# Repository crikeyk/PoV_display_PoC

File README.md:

# PoV display

A hand-waved persistence-of-vision wand. A strip of 16 LEDs and an accelerometer draw a word or a picture in the air.

## What goes on the wand

`Firmware/device/` is the CircuitPython image for the RP2350 (Pico 2) wand. Copy the files inside that folder onto the `CIRCUITPY` drive. `code.py` there is version 7.

A Pico that has never been used needs CircuitPython first. Hold BOOTSEL while plugging it in so a drive named `RP2350` appears, copy `Firmware/circuitpython-pico2-10.3.1.uf2` onto it, then copy `Firmware/device/`.

`README.txt` inside that folder is the note for whoever changes the words.

## What does not go on the wand

`Firmware/debug/` records a swing and draws it in a browser. `Firmware/tests/` are early hardware checks. `Firmware/ch572/` is a different board.

## Older firmware

Version 6 was the last stable program before version 7 froze the pace for each pass. It is the git tag `v6`. In that tag the program is `Firmware/device_pull_v1/code.py`.

`AGENTS.md` is the longer note for a person or a coding agent picking this up.

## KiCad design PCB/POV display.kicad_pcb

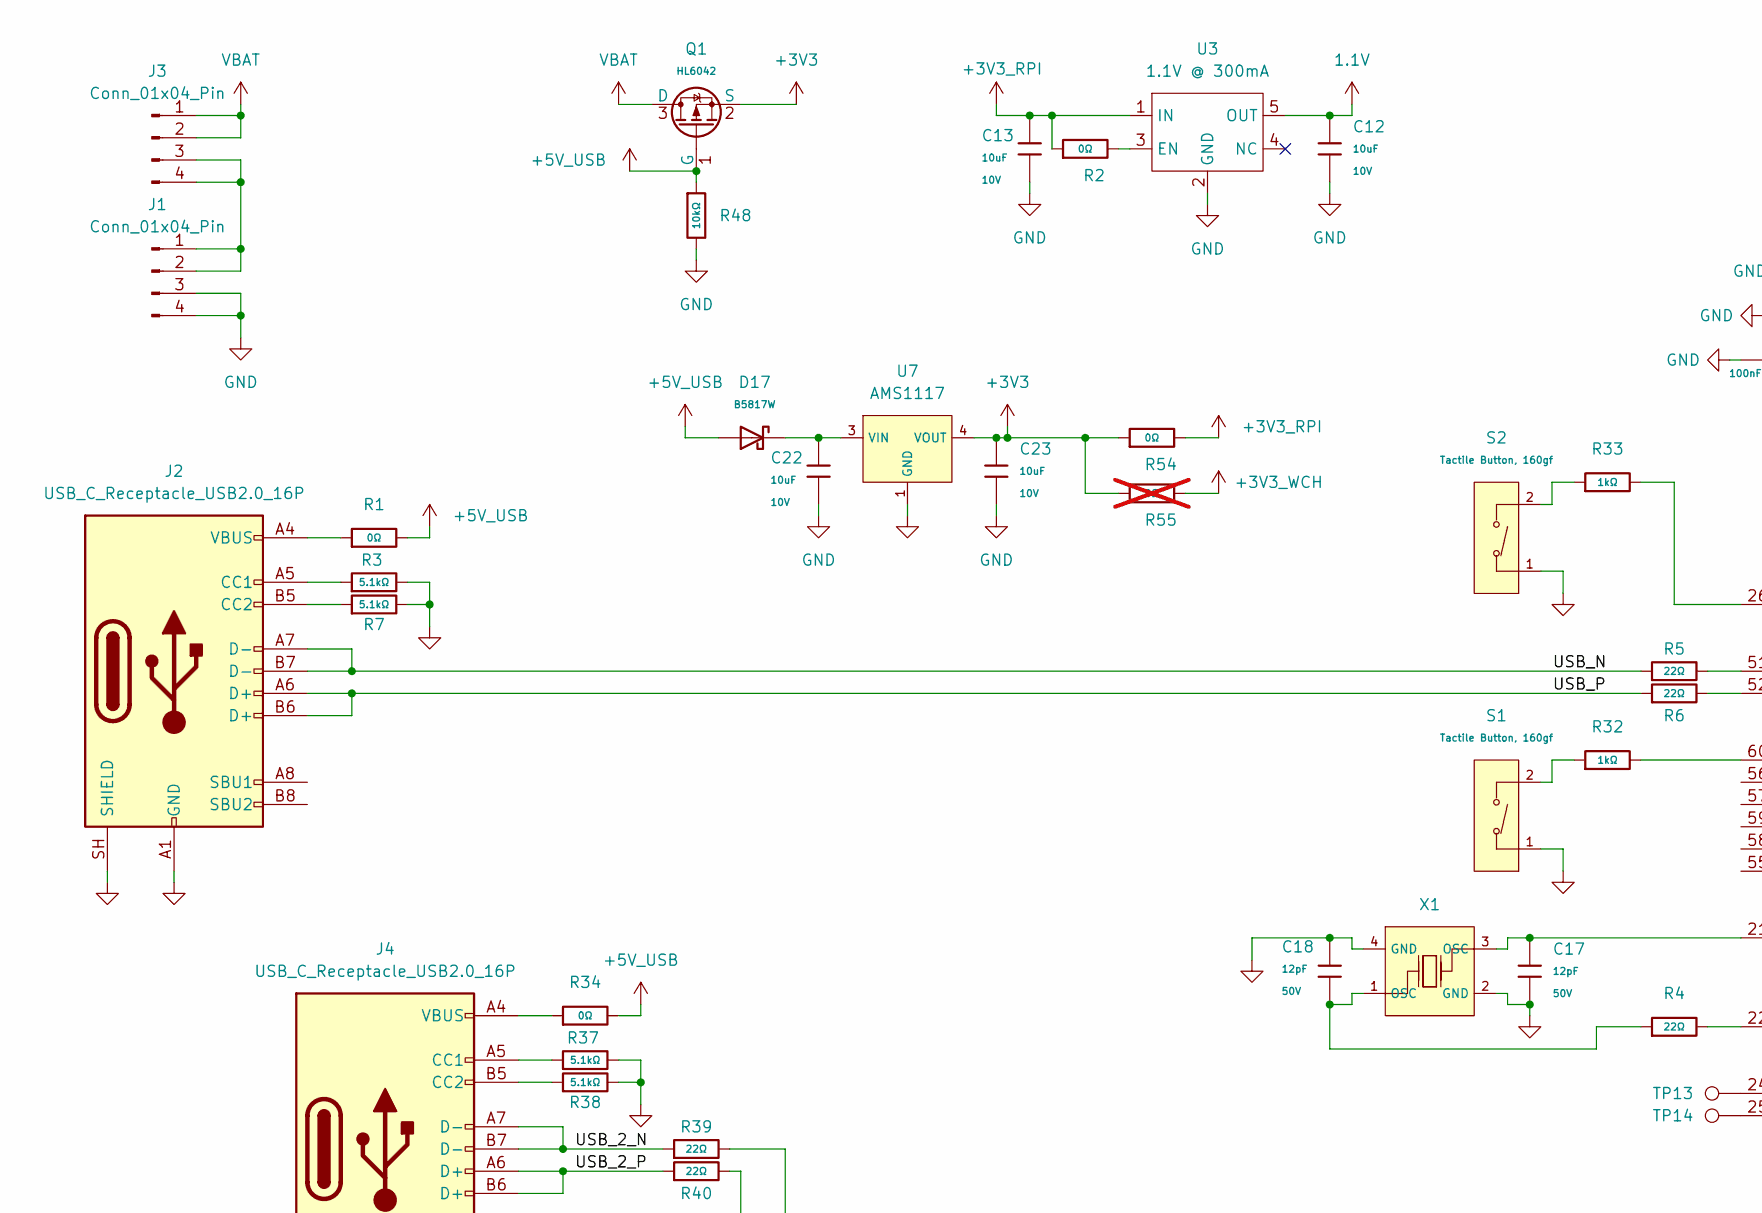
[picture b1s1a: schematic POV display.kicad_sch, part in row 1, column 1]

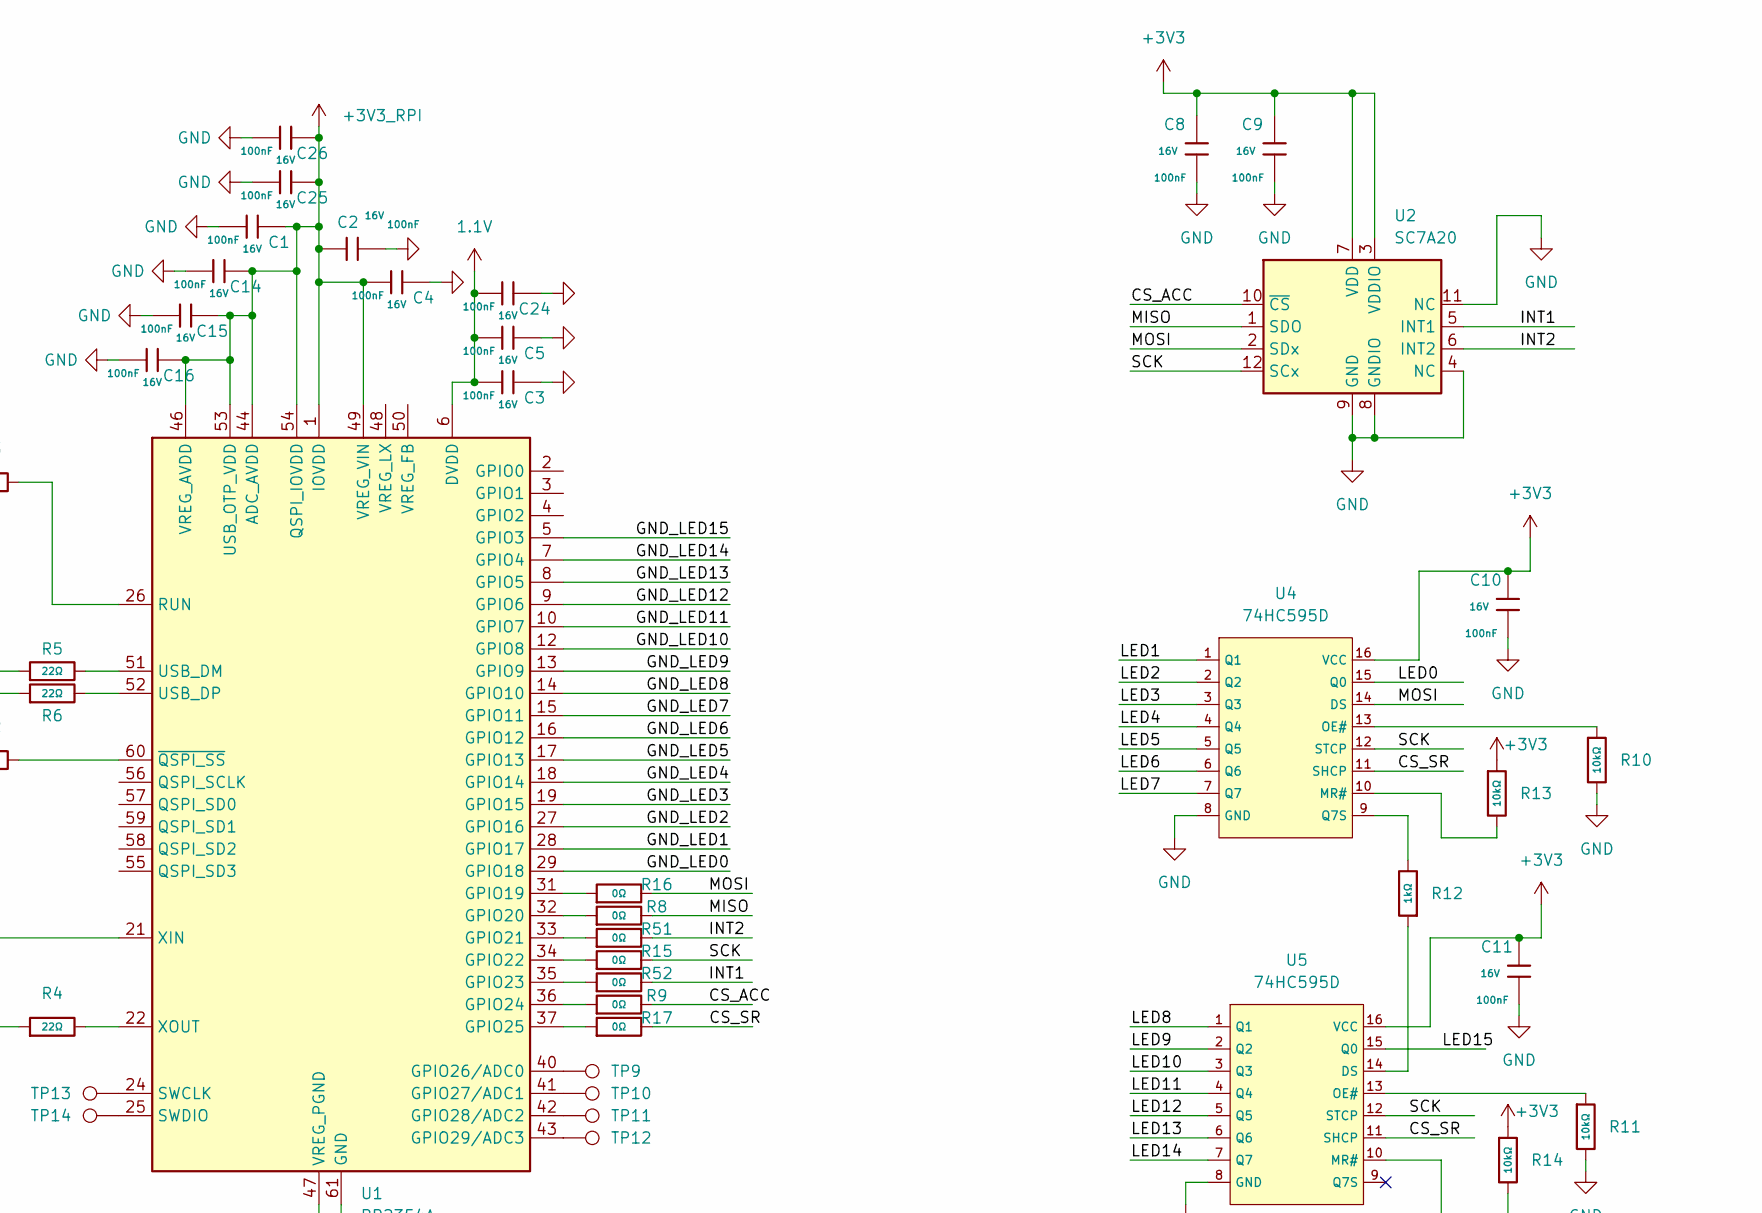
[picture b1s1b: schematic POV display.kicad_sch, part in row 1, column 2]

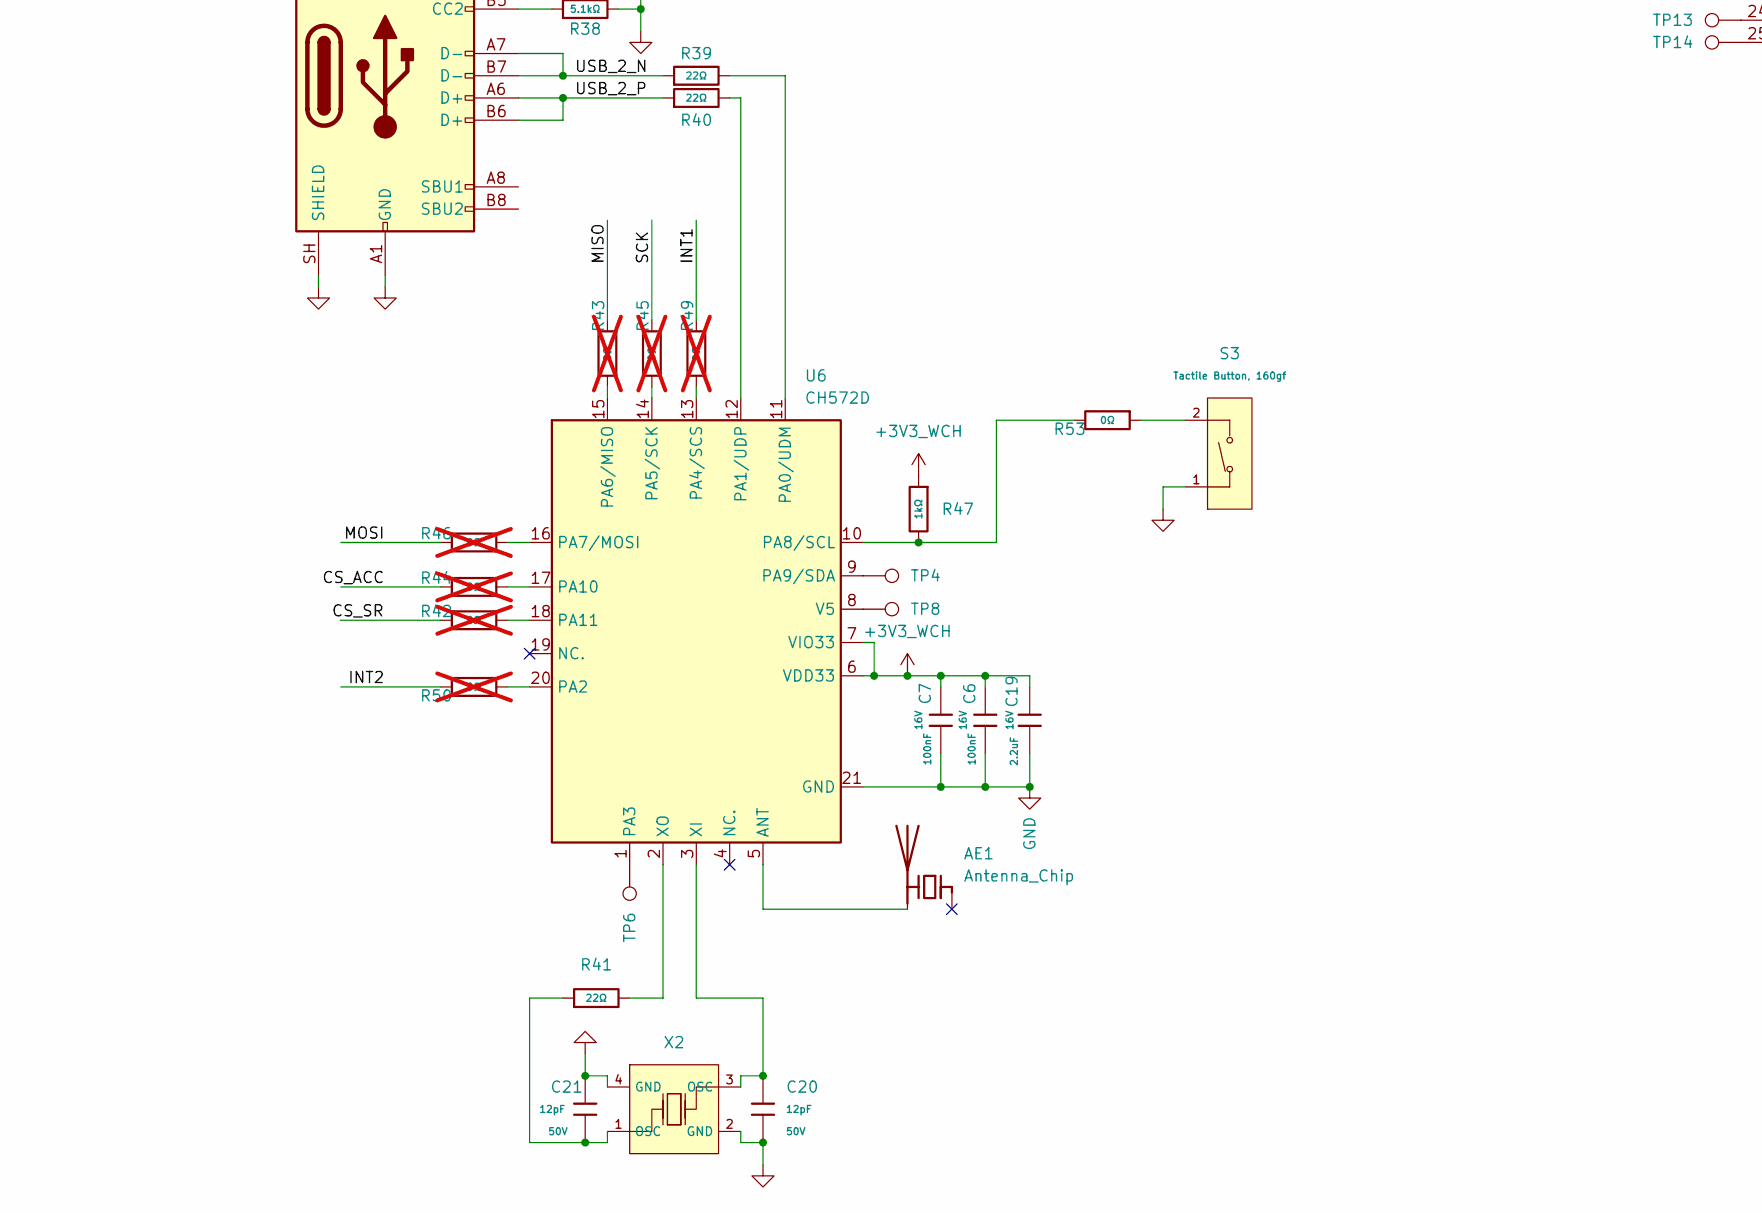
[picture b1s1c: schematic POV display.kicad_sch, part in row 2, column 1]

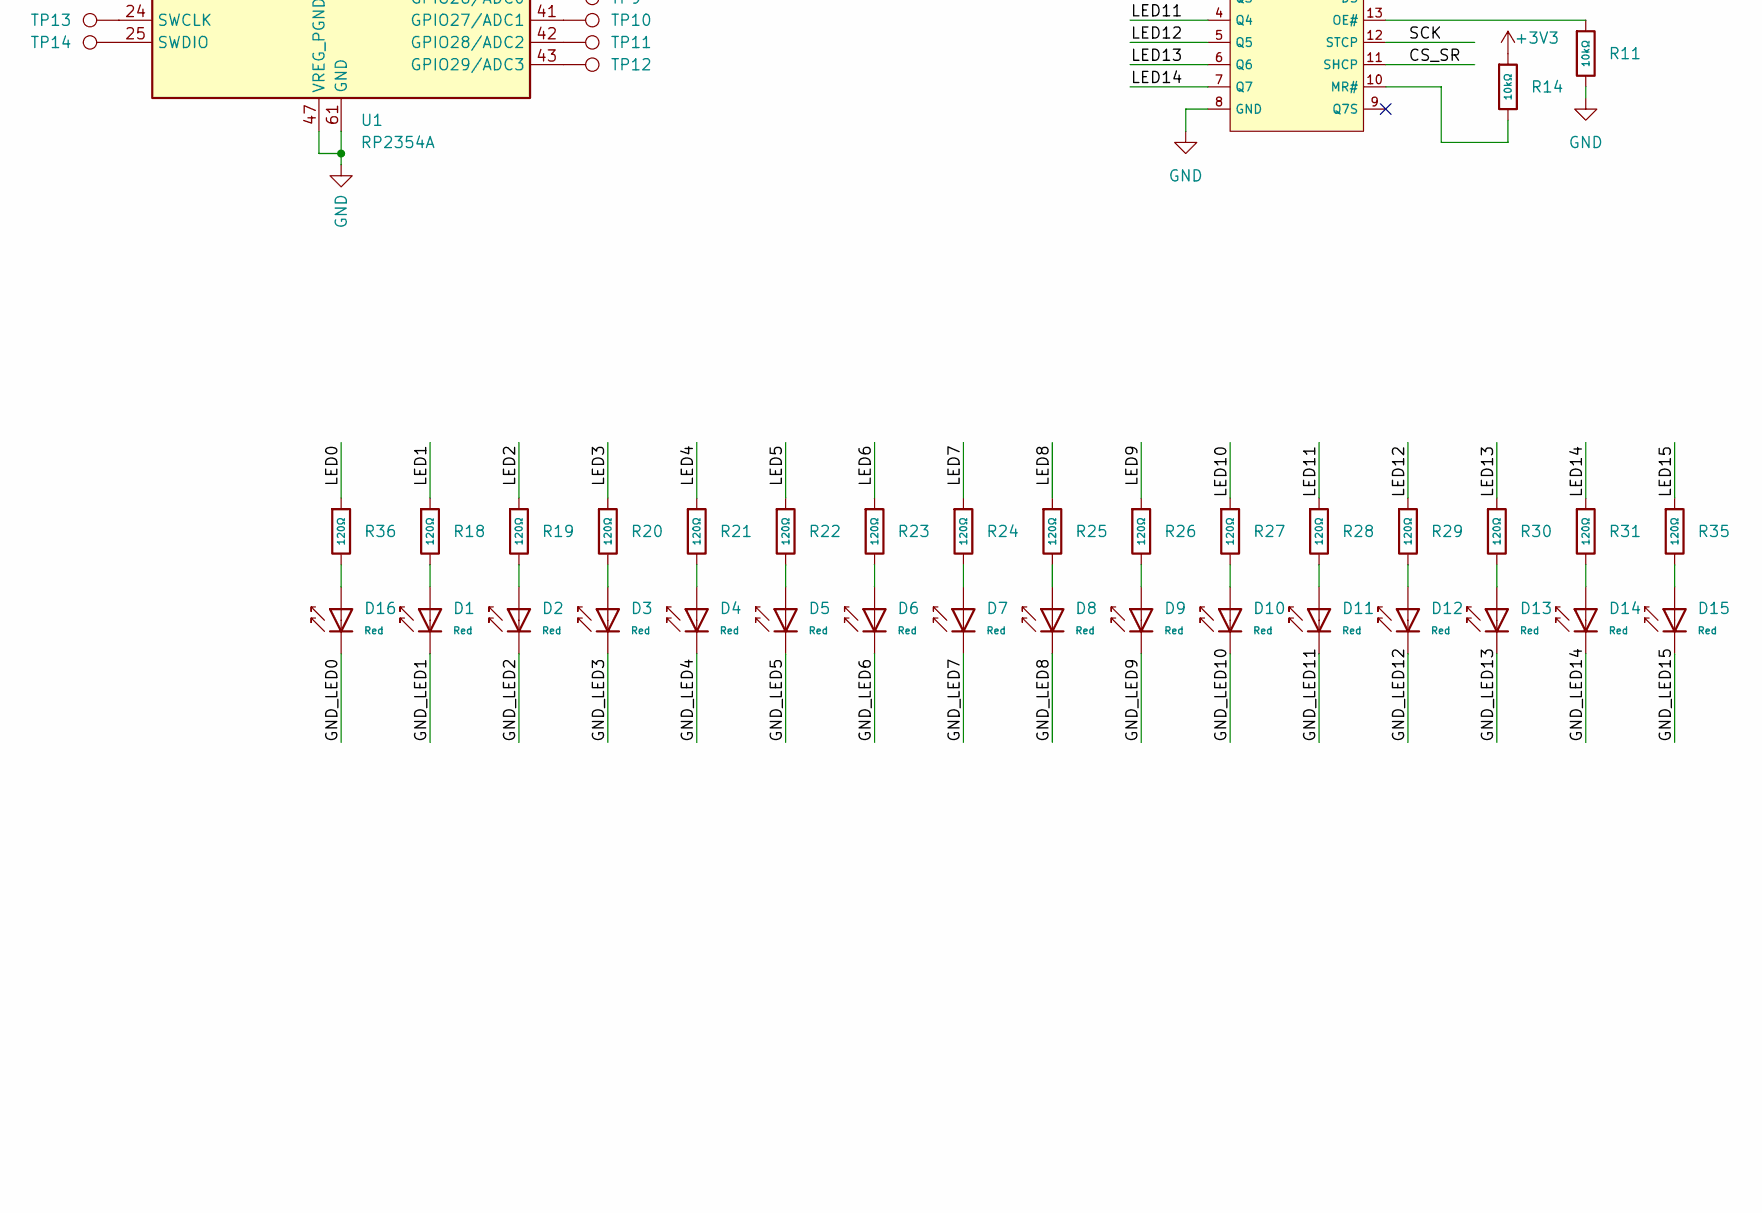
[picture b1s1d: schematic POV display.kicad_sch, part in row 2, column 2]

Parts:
AE1: Antenna_Chip; C_1206_3216Metric; LCSC C127629
C1, C2, C3, C4, C5, C6, C7, C8, C9, C10, C11, C14, C15, C16, C24, C25, C26: 100nF; C_0402; Voltage Rated 16V; Tolerance ±10%; Part CL05B104KO5NNNC; LCSC C1525
C12, C13, C22, C23: 10uF; C_0603; Voltage Rated 10V; Tolerance ±10%; Part CL10A106KP8NNNC; LCSC C19702
C17, C18, C20, C21: 12pF; C_0402; Voltage Rated 50V; Tolerance ±5%; Part 0402CG120J500NT; LCSC C1547
C19: 2.2uF; C_0603; Voltage Rated 16V; Tolerance ±10%; Part CL10A225KO8NNNC; LCSC C23630
D1, D2, D3, D4, D5, D6, D7, D8, D9, D10, D11, D12, D13, D14, D15, D16: Red; D_0603; Part KT-0603R; LCSC C2286
D17: B5817W; D_SOD-123; Forward Voltage (Vf@If) 0.45V@1.0A; Reverse Voltage (Vr) 20V; Part B5817W; LCSC C7420328
J1, J3: Conn_01x04_Pin; BC-8200 AAA Battery clip
J2, J4: USB_C_Receptacle_USB2.0_16P; USB_C_Receptacle_HRO_TYPE-C-31-M-12; LCSC C165948
Q1: HL6042; Q_SOT-23; Part HL6042; LCSC C28646264
R1, R2, R8, R9, R15, R16, R17, R34, R51, R52, R53, R54: 0Ω; R_0402; Overload Voltage (Max) 50V; Tolerance ±1%; Part 0402WGF0000TCE; LCSC C17168
R3, R7, R37, R38: 5.1kΩ; R_0402; Overload Voltage (Max) 50V; Tolerance ±1%; Part 0402WGF5101TCE; LCSC C25905
R4, R5, R6, R39, R40, R41: 22Ω; R_0402; Overload Voltage (Max) 50V; Tolerance ±1%; Part 0402WGF220JTCE; LCSC C25092
R10, R11, R13, R14: 10kΩ; R_0603; Overload Voltage (Max) 75V; Tolerance ±1%; Part 0603WAF1002T5E; LCSC C25804
R12: 1kΩ; R_0603; Overload Voltage (Max) 75V; Tolerance ±1%; Part 0603WAF1001T5E; LCSC C21190
R18, R19, R20, R21, R22, R23, R24, R25, R26, R27, R28, R29, R30, R31, R35, R36: 120Ω; R_0603; Overload Voltage (Max) 75V; Tolerance ±1%; Part 0603WAF1200T5E; LCSC C22787
R32, R33, R47: 1kΩ; R_0402; Overload Voltage (Max) 50V; Tolerance ±1%; Part 0402WGF1001TCE; LCSC C11702
R42, R43, R44, R45, R46, R49, R50, R55: 0Ω; R_0402; Overload Voltage (Max) 50V; Tolerance ±1%; Part 0402WGF0000TCE; LCSC C17168; not fitted
R48: 10kΩ; R_0402; Overload Voltage (Max) 50V; Tolerance ±1%; Part 0402WGF1002TCE; LCSC C25744
S1, S2, S3: Tactile Button, 160gf; SW_TS-1088-AR02016; Voltage Rating (Dc) 12V; Part TS-1088-AR02016; LCSC C720477
TP4, TP6, TP8, TP9, TP10, TP11, TP12, TP13, TP14: TestPoint; TestPoint_Pad_D1.0mm
U1: RP2354A; QFN-60-1EP_7x7mm_P0.4mm_EP3.4x3.4mm; LCSC C41378174
U2: SC7A20; LGA-12_2x2mm_P0.5mm; LCSC C19274408
U3: 1.1V @ 300mA; SOT-23-5; LCSC C485147
U4, U5: 74HC595D; SOIC-16_L9.9-W3.9-P1.27-LS6.0-BL; Supply Voltage 2V~6V; Part 74HC595D,118; LCSC C5947
U6: CH572D; QFN-20-1EP_3x3mm_P0.4mm_EP1.65x1.65mm
U7: AMS1117; SOT-223-3_L6.5-W3.4-P2.30-LS7.0-BR; Output Voltage 3.3V; Dropout Voltage 1.3V@(800mA); Part AMS1117-3.3; LCSC C6186
X1: X322512MSB4SI; CRYSTAL-SMD_4P-L3.2-W2.5-BL; Frequency Tolerance ±10ppm; Part X322512MSB4SI; LCSC C9002
X2: Y201632MFBCX; Crystal_SMD_2016-4Pin_2.0x1.6mm; Frequency Tolerance ±10ppm; Part Y201632MFBCX; LCSC C49158176

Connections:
1.1V: C3.2, C5.2, C12.1, C24.2, U1.6 (DVDD), U1.23 (DVDD), U1.39 (DVDD), U3.5 (OUT)
+3V3: C8.1, C9.1, C10.1, C11.1, C23.1, Q1.2 (S), R13.1, R14.1, R54.1, R55.1, U2.3 (VDDIO), U2.7 (VDD), U4.16 (VCC), U5.16 (VCC), U7.2 (VOUT), U7.4 (VOUT)
+3V3_RPI: C1.1, C2.1, C4.2, C13.1, C14.1, C15.1, C16.1, C25.1, C26.1, R2.1, R54.2, U1.1 (IOVDD), U1.11 (IOVDD), U1.20 (IOVDD), U1.30 (IOVDD), U1.38 (IOVDD), U1.44 (ADC_AVDD), U1.45 (IOVDD), U1.46 (VREG_AVDD), U1.49 (VREG_VIN), U1.53 (USB_OTP_VDD), U1.54 (QSPI_IOVDD), U3.1 (IN)
+3V3_WCH: C6.1, C7.1, C19.1, R47.1, R55.2, U6.6 (VDD33), U6.7 (VIO33)
+5V_USB: D17.2, Q1.1 (G), R1.2, R34.2, R48.1
/CS_ACC: R9.2, R44.2, U2.10 (~CS)
/CS_SR: R17.2, R42.2, U4.11 (SHCP), U5.11 (SHCP)
/GND_LED0: D16.1, U1.29 (GPIO18)
/GND_LED1: D1.1, U1.28 (GPIO17)
/GND_LED2: D2.1, U1.27 (GPIO16)
/GND_LED3: D3.1, U1.19 (GPIO15)
/GND_LED4: D4.1, U1.18 (GPIO14)
/GND_LED5: D5.1, U1.17 (GPIO13)
/GND_LED6: D6.1, U1.16 (GPIO12)
/GND_LED7: D7.1, U1.15 (GPIO11)
/GND_LED8: D8.1, U1.14 (GPIO10)
/GND_LED9: D9.1, U1.13 (GPIO9)
/GND_LED10: D10.1, U1.12 (GPIO8)
/GND_LED11: D11.1, U1.10 (GPIO7)
/GND_LED12: D12.1, U1.9 (GPIO6)
/GND_LED13: D13.1, U1.8 (GPIO5)
/GND_LED14: D14.1, U1.7 (GPIO4)
/GND_LED15: D15.1, U1.5 (GPIO3)
/INT1: R49.2, R52.2, U2.5 (INT1)
/INT2: R50.2, R51.2, U2.6 (INT2)
/LED0: R36.1, U4.15 (Q0)
/LED1: R18.1, U4.1 (Q1)
/LED2: R19.1, U4.2 (Q2)
/LED3: R20.1, U4.3 (Q3)
/LED4: R21.1, U4.4 (Q4)
/LED5: R22.1, U4.5 (Q5)
/LED6: R23.1, U4.6 (Q6)
/LED7: R24.1, U4.7 (Q7)
/LED8: R25.1, U5.1 (Q1)
/LED9: R26.1, U5.2 (Q2)
/LED10: R27.1, U5.3 (Q3)
/LED11: R28.1, U5.4 (Q4)
/LED12: R29.1, U5.5 (Q5)
/LED13: R30.1, U5.6 (Q6)
/LED14: R31.1, U5.7 (Q7)
/LED15: R35.1, U5.15 (Q0)
/MISO: R8.2, R43.2, U2.1 (SDO)
/MOSI: R16.2, R46.2, U2.2 (SDx), U4.14 (DS)
/SCK: R15.2, R45.2, U2.12 (SCx), U4.12 (STCP), U5.12 (STCP)
/USB_2_N: J4.A7 (D-), J4.B7 (D-), R39.1
/USB_2_P: J4.A6 (D+), J4.B6 (D+), R40.1
/USB_N: J2.A7 (D-), J2.B7 (D-), R5.1
/USB_P: J2.A6 (D+), J2.B6 (D+), R6.1
GND: C1.2, C2.2, C3.1, C4.1, C5.1, C6.2, C7.2, C8.2, C9.2, C10.2, C11.2, C12.2, C13.2, C14.2, C15.2, C16.2, C17.2, C18.2, C19.2, C20.2, C21.2, C22.2, C23.2, C24.1, C25.2, C26.2, J1.3, J1.4, J2.A1 (GND), J2.A12 (GND), J2.B1 (GND), J2.B12 (GND), J2.SH (SHIELD), J4.A1 (GND), J4.A12 (GND), J4.B1 (GND), J4.B12 (GND), J4.SH (SHIELD), R3.2, R7.2, R10.2, R11.2, R37.2, R38.2, R48.2, S1.1 (A), S2.1 (A), S3.1 (A), U1.47 (VREG_PGND), U1.61 (GND), U2.4 (NC), U2.8 (GNDIO), U2.9 (GND), U2.11 (NC), U3.2 (GND), U4.8 (GND), U5.8 (GND), U6.21 (GND), U7.1 (GND), X1.2 (GND), X1.4 (GND), X2.2 (GND), X2.4 (GND)
unnamed: AE1.2 (PCB_Trace_2), U6.5 (ANT)
unnamed: C18.1, R4.1, X1.1 (OSC)
unnamed: C21.1, R41.1, X2.1 (OSC)
unnamed: D1.2, R18.2
unnamed: D2.2, R19.2
unnamed: D3.2, R20.2
unnamed: D4.2, R21.2
unnamed: D5.2, R22.2
unnamed: D6.2, R23.2
unnamed: D7.2, R24.2
unnamed: D8.2, R25.2
unnamed: D9.2, R26.2
unnamed: D10.2, R27.2
unnamed: D11.2, R28.2
unnamed: D12.2, R29.2
unnamed: D13.2, R30.2
unnamed: D14.2, R31.2
unnamed: D15.2, R35.2
unnamed: D16.2, R36.2
unnamed: J1.1, J1.2, J3.3, J3.4
unnamed: J2.A5 (CC1), R3.1
unnamed: J2.B5 (CC2), R7.1
unnamed: J2.A4 (VBUS), J2.A9 (VBUS), J2.B4 (VBUS), J2.B9 (VBUS), R1.1
unnamed: J4.A5 (CC1), R37.1
unnamed: J4.B5 (CC2), R38.1
unnamed: J4.A4 (VBUS), J4.A9 (VBUS), J4.B4 (VBUS), J4.B9 (VBUS), R34.1
unnamed: R32.1, S1.2 (B)
unnamed: R33.1, S2.2 (B)
unnamed: R53.1, S3.2 (B)
unnamed: R16.1, U1.31 (GPIO19)
unnamed: R8.1, U1.32 (GPIO20)
unnamed: R51.1, U1.33 (GPIO21)
unnamed: R15.1, U1.34 (GPIO22)
unnamed: R52.1, U1.35 (GPIO23)
unnamed: R9.1, U1.36 (GPIO24)
unnamed: R17.1, U1.37 (GPIO25)
unnamed: TP9.1 (1_1), U1.40 (GPIO26/ADC0)
unnamed: TP10.1 (1_1), U1.41 (GPIO27/ADC1)
unnamed: TP11.1 (1_1), U1.42 (GPIO28/ADC2)
unnamed: TP12.1 (1_1), U1.43 (GPIO29/ADC3)
unnamed: R33.2, U1.26 (RUN)
unnamed: TP13.1 (1_1), U1.24 (SWCLK)
unnamed: TP14.1 (1_1), U1.25 (SWDIO)
unnamed: R5.2, U1.51 (USB_DM)
unnamed: R6.2, U1.52 (USB_DP)
unnamed: C17.1, U1.21 (XIN), X1.3 (OSC)
unnamed: R4.2, U1.22 (XOUT)
unnamed: R32.2, U1.60 (~QSPI_SS)
unnamed: R2.2, U3.3 (EN)
unnamed: R13.2, U4.10 (MR#)
unnamed: R10.1, U4.13 (OE#)
unnamed: R12.2, U4.9 (Q7S)
unnamed: R12.1, U5.14 (DS)
unnamed: R14.2, U5.10 (MR#)
unnamed: R11.1, U5.13 (OE#)
unnamed: R39.2, U6.11 (PA0/UDM)
unnamed: R40.2, U6.12 (PA1/UDP)
unnamed: R50.1, U6.20 (PA2)
unnamed: TP6.1 (1_1), U6.1 (PA3)
unnamed: R49.1, U6.13 (PA4/SCS)
unnamed: R45.1, U6.14 (PA5/SCK)
unnamed: R43.1, U6.15 (PA6/MISO)
unnamed: R46.1, U6.16 (PA7/MOSI)
unnamed: R47.2, R53.2, U6.10 (PA8/SCL)
unnamed: TP4.1 (1_1), U6.9 (PA9/SDA)
unnamed: R44.1, U6.17 (PA10)
unnamed: R42.1, U6.18 (PA11)
unnamed: TP8.1 (1_1), U6.8 (V5)
unnamed: C20.1, U6.3 (XI), X2.3 (OSC)
unnamed: R41.2, U6.2 (XO)
unnamed: C22.1, D17.1, U7.3 (VIN)
VBAT: J3.1, J3.2, Q1.3 (D)

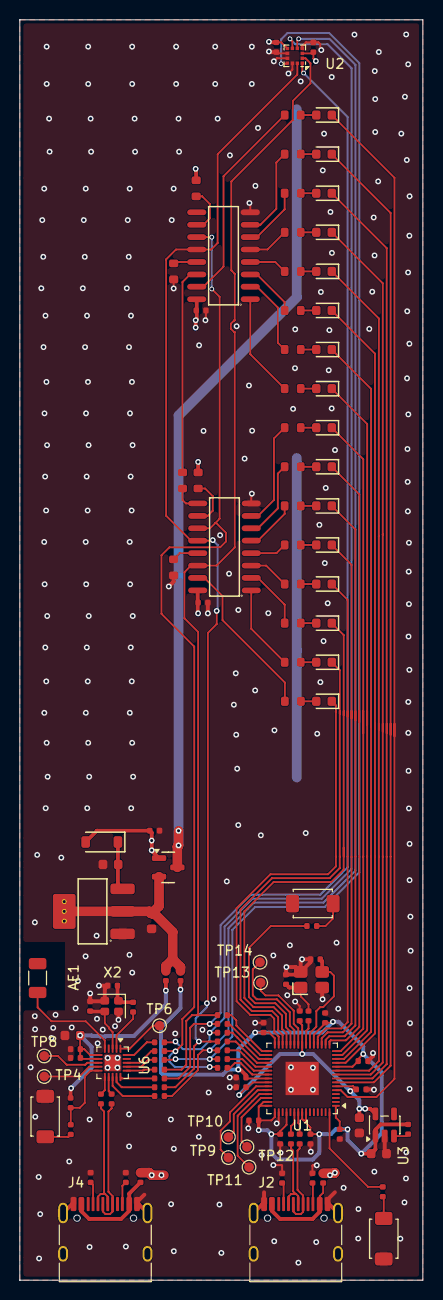
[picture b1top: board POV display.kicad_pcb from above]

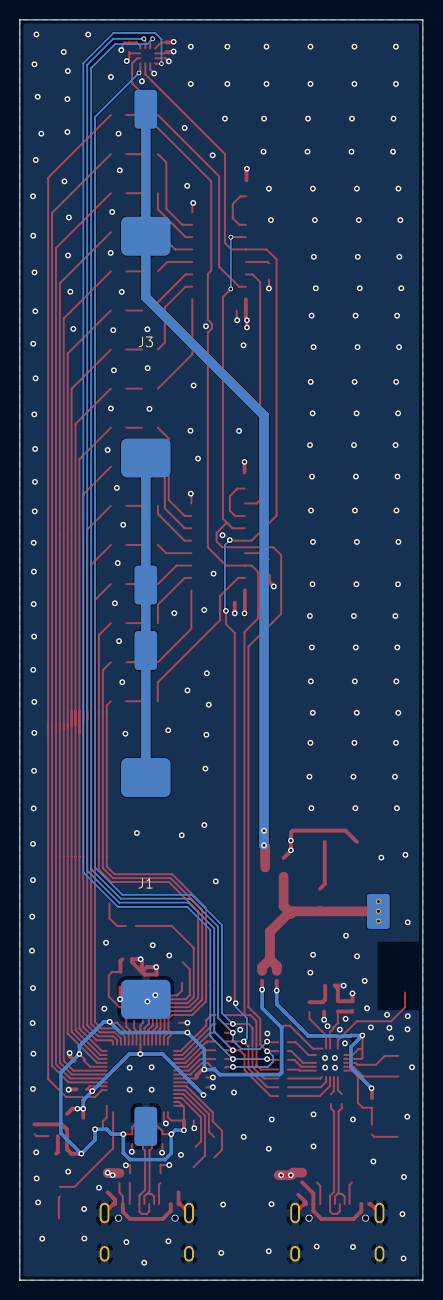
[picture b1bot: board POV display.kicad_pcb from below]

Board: 4 copper layers, 41.2 x 129.0 mm, 125 parts (2 on the bottom side), 121 nets.

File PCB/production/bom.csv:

Designator,Footprint,Quantity,Value,LCSC Part #
AE1,1206,1,Antenna_Chip,C127629
"C1, C10, C11, C14, C15, C16, C2, C24, C25, C26, C3, C4, C5, C6, C7, C8, C9",C_0402,17,100nF,C1525
"C12, C13, C22, C23",C_0603,4,10uF,C19702
"C17, C18, C20, C21",C_0402,4,12pF,C1547
C19,C_0603,1,2.2uF,C23630
"D1, D10, D11, D12, D13, D14, D15, D16, D2, D3, D4, D5, D6, D7, D8, D9",D_0603,16,Red,C2286
D17,D_SOD-123,1,B5817W,C7420328
"J1, J3",BC-8200 AAA Battery clip,2,Conn_01x04_Pin,
"J2, J4",USB_C_Receptacle_HRO_TYPE-C-31-M-12,2,USB_C_Receptacle_USB2.0_16P,C165948
Q1,Q_SOT-23,1,HL6042,C28646264
"R1, R15, R16, R17, R2, R34, R42, R43, R44, R45, R46, R49, R50, R51, R52, R53, R54, R55, R8, R9",R_0402,20,0Ω,C17168
"R10, R11, R13, R14",R_0603,4,10kΩ,C25804
R12,R_0603,1,1kΩ,C21190
"R18, R19, R20, R21, R22, R23, R24, R25, R26, R27, R28, R29, R30, R31, R35, R36",R_0603,16,120Ω,C22787
"R3, R37, R38, R7",R_0402,4,5.1kΩ,C25905
"R32, R33, R47",R_0402,3,1kΩ,C11702
"R39, R4, R40, R41, R5, R6",R_0402,6,22Ω,C25092
R48,R_0402,1,10kΩ,C25744
"S1, S2, S3",SW_TS-1088-AR02016,3,"Tactile Button, 160gf",C720477
"TP10, TP11, TP12, TP13, TP14, TP4, TP6, TP8, TP9",TestPoint_Pad_D1.0mm,9,TestPoint,
U1,QFN-60-1EP_7x7mm_P0.4mm_EP3.4x3.4mm,1,RP2354A,C41378174
U2,LGA-12_2x2mm_P0.5mm,1,SC7A20,
U3,SOT-23-5,1,1.1V @ 300mA,C485147
"U4, U5",SOIC-16_L9.9-W3.9-P1.27-LS6.0-BL,2,74HC595D,C5947
U6,QFN-20-1EP_3x3mm_P0.4mm_EP1.65x1.65mm,1,CH572D,
U7,SOT-223-3_L6.5-W3.4-P2.30-LS7.0-BR,1,AMS1117,C6186
X1,CRYSTAL-SMD_4P-L3.2-W2.5-BL,1,X322512MSB4SI,C9002
X2,Crystal_SMD_2016-4Pin_2.0x1.6mm,1,Y201632MFBCX,C49158176

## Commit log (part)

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2026-05-04 moved README.md
